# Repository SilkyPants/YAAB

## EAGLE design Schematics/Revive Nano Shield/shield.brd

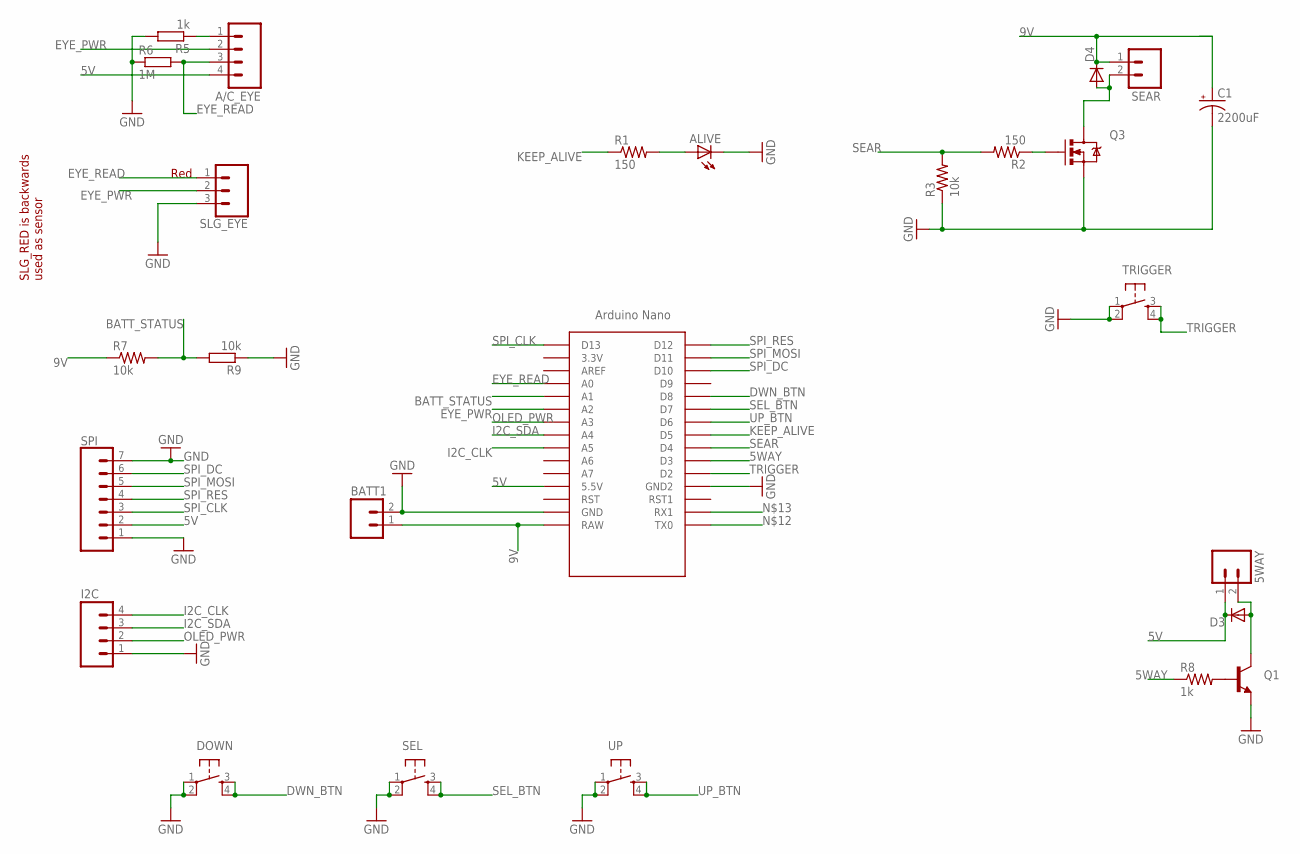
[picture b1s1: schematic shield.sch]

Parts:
5WAY: M02PTH; 1X02
A/C_EYE: M04PTH; 1X04
ALIVE: LED3MM
BATT1: M02PTH; 1X02
C1: 2200uF; CPOL-RADIAL-1000UF-25V
D3, D4: DIODEPTH; DIODE-1N4001
DOWN: TAC_SWITCHPTH; TACTILE-PTH
I2C: M04PTH; 1X04
Q1: TRANSISTOR_NPNTO-92-AMMO; TO-92-AMMO
Q3: MOSFET-NCHANNELPTH2; TO220V
R1, R2: 150; AXIAL-0.4
R3, R7: 10k; AXIAL-0.4
R5: 1k; 0309V
R6: 1M; 0309V
R8: 1k; AXIAL-0.4
R9: 10k; 0309V
SEAR: M02PTH; 1X02
SEL: TAC_SWITCHPTH; TACTILE-PTH
SLG_EYE: CONN_03; 1X03
SPI: CONN_07; 1X07
TRIGGER: TAC_SWITCHPTH; TACTILE-PTH
U$5: NANO
UP: TAC_SWITCHPTH; TACTILE-PTH

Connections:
5V: 5WAY.1, A/C_EYE.4, D3.C, SPI.2, U$5.5V (5.5V)
5WAY: R8.P$1 (1), U$5.D3
9V: BATT1.1, C1.1 (+), D4.C, R7.P$1 (1), SEAR.1, U$5.RAW
BATT_STATUS: R7.P$2 (2), R9.2, U$5.A1
DWN_BTN: DOWN.3, DOWN.4, U$5.D8
EYE_GND: A/C_EYE.1, R5.1
EYE_PWR: A/C_EYE.2, SLG_EYE.2, U$5.A2
EYE_READ: A/C_EYE.3, R6.2, SLG_EYE.1, U$5.A0
GND: ALIVE.K (C), BATT1.2, C1.2 (-), DOWN.1, DOWN.2, I2C.1, Q1.1 (E), Q3.3 (S), R3.P$1 (1), R5.2, R6.1, R9.1, SEL.1, SEL.2, SLG_EYE.3, SPI.1, SPI.7, TRIGGER.1, TRIGGER.2, U$5.GND, U$5.GND1 (GND2), UP.1, UP.2
I2C_CLK: I2C.4, U$5.A5
I2C_SDA: I2C.3, U$5.A4
KEEP_ALIVE: R1.P$1 (1), U$5.D5
unnamed: Q1.2 (B), R8.P$2 (2)
unnamed: ALIVE.A, R1.P$2 (2)
unnamed: Q3.1 (G), R2.P$1 (1)
unnamed: D4.A, Q3.2 (D), SEAR.2
unnamed: 5WAY.2, D3.A, Q1.3 (C)
OLED_PWR: I2C.2, U$5.A3
SEAR: R2.P$2 (2), R3.P$2 (2), U$5.D4
SEL_BTN: SEL.3, SEL.4, U$5.D7
SPI_CLK: SPI.3, U$5.D13
SPI_DC: SPI.6, U$5.D10
SPI_MOSI: SPI.5, U$5.D11
SPI_RES: SPI.4, U$5.D12
TRIGGER: TRIGGER.3, TRIGGER.4, U$5.D2
UP_BTN: U$5.D6, UP.3, UP.4

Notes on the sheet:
SLG_RED is backwards used as sensor
Red

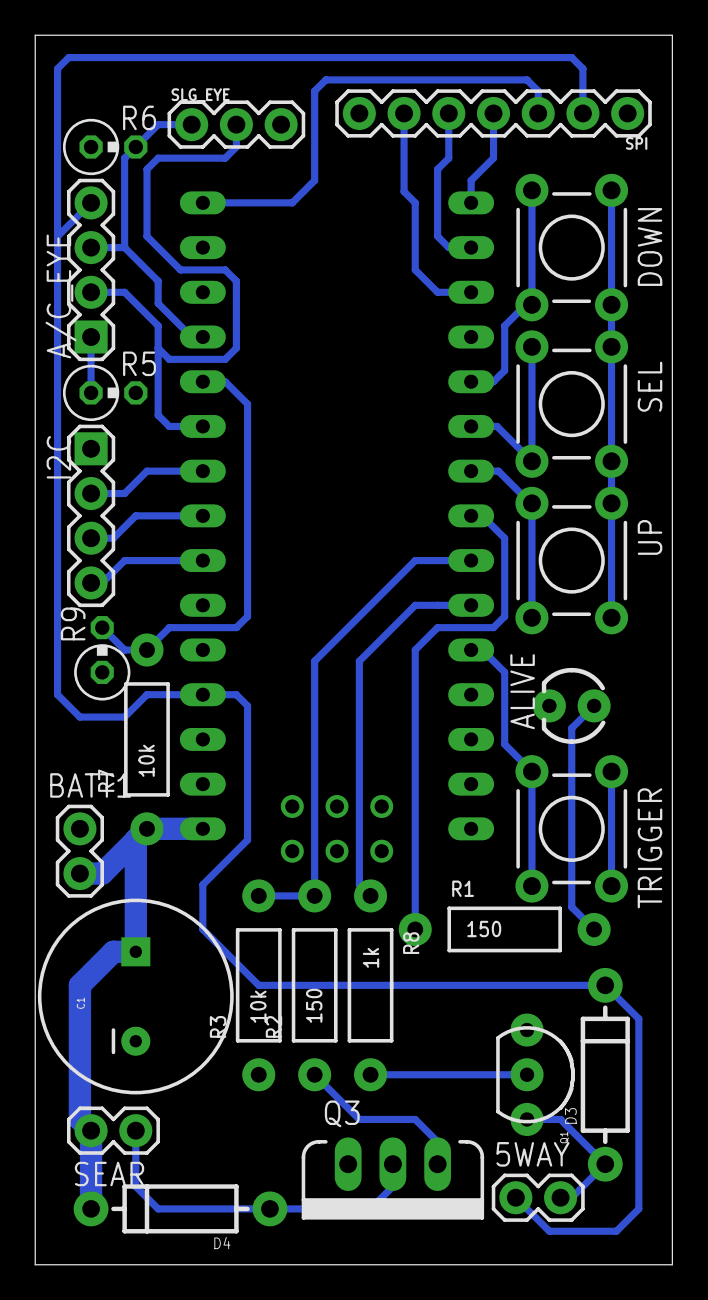
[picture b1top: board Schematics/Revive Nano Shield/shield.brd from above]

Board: 2 copper layers, 36.2 x 69.8 mm, 26 parts (0 on the bottom side), 26 nets.

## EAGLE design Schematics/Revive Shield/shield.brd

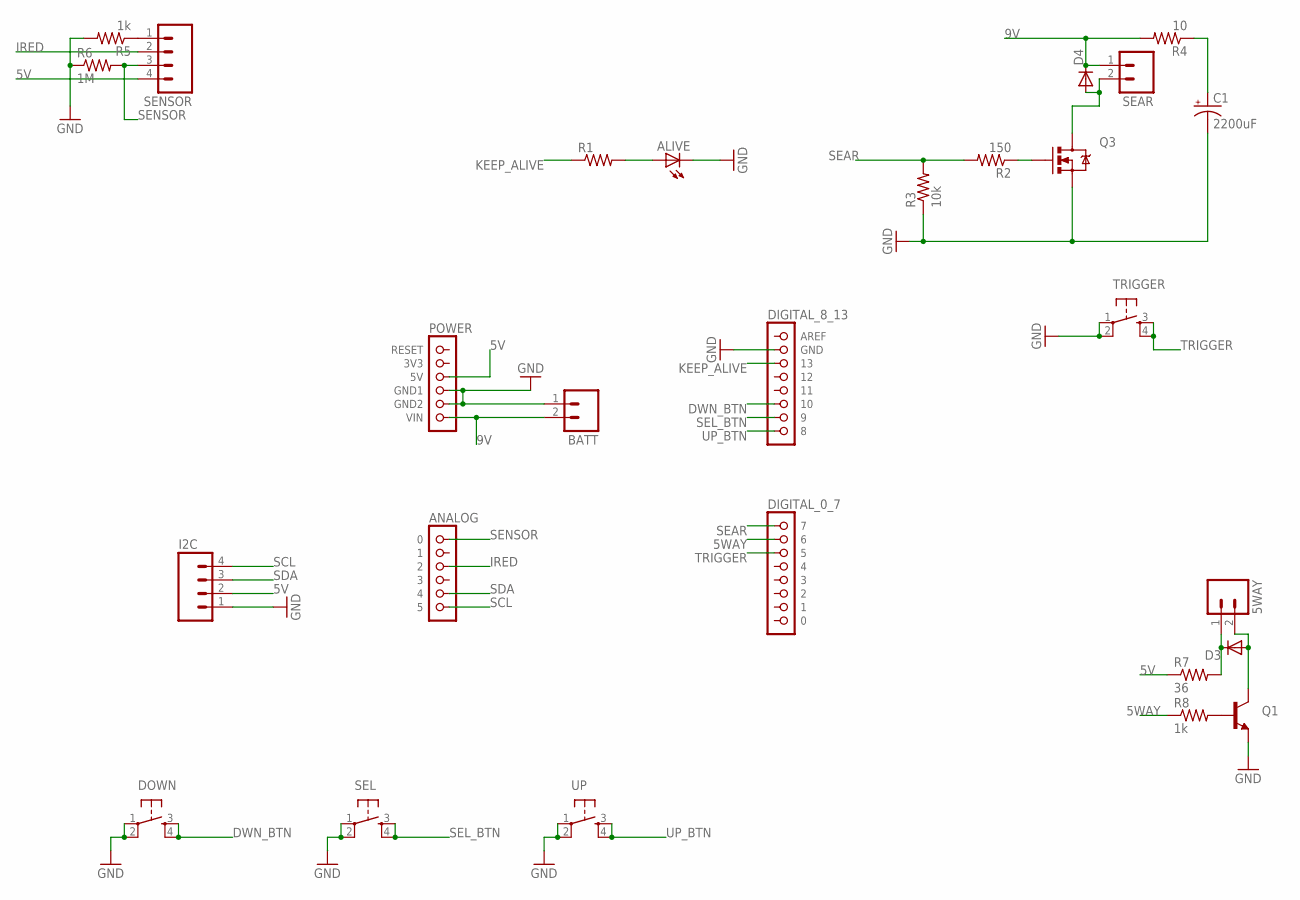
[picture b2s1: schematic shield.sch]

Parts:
5WAY: M02PTH; 1X02
ALIVE: LED3MM
BATT: M02PTH; 1X02
C1: 2200uF; CPOL-RADIAL-1000UF-25V
D3, D4: DIODEPTH; DIODE-1N4001
DOWN: TAC_SWITCHPTH; TACTILE-PTH
I2C: M04PTH; 1X04
Q1: TRANSISTOR_NPNTO-92-AMMO; TO-92-AMMO
Q3: MOSFET-NCHANNELPTH2; TO220V
R1: RESISTORPTH-1/4W; AXIAL-0.4
R2: 150; AXIAL-0.4
R3: 10k; AXIAL-0.4
R4: 10; AXIAL-0.4
R5, R8: 1k; AXIAL-0.4
R6: 1M; AXIAL-0.4
R7: 36; AXIAL-0.4
SEAR: M02PTH; 1X02
SEL: TAC_SWITCHPTH; TACTILE-PTH
SENSOR: M04PTH; 1X04
TRIGGER: TAC_SWITCHPTH; TACTILE-PTH
U$1: POWER; 1X06
U$2: ANALOG; 1X06
U$3: DIGITAL_0_7; 1X08
U$4: DIGITAL_8_13; 1X08
UP: TAC_SWITCHPTH; TACTILE-PTH

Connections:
5V: I2C.2, R7.P$1 (1), SENSOR.4, U$1.3 (5V)
5WAY: R8.P$1 (1), U$3.2 (6)
9V: BATT.2, D4.C, R4.P$2 (2), SEAR.1, U$1.6 (VIN)
DWN_BTN: DOWN.3, DOWN.4, U$4.6 (10)
GND: ALIVE.K (C), BATT.1, C1.2 (-), DOWN.1, DOWN.2, I2C.1, Q1.1 (E), Q3.3 (S), R3.P$1 (1), R5.P$2 (2), R6.P$1 (1), SEL.1, SEL.2, TRIGGER.1, TRIGGER.2, U$1.4 (GND1), U$1.5 (GND2), U$4.2 (GND), UP.1, UP.2
IRED: SENSOR.2, U$2.3 (2)
KEEP_ALIVE: R1.P$1 (1), U$4.3 (13)
unnamed: Q1.2 (B), R8.P$2 (2)
unnamed: ALIVE.A, R1.P$2 (2)
unnamed: Q3.1 (G), R2.P$1 (1)
unnamed: C1.1 (+), R4.P$1 (1)
unnamed: 5WAY.1, D3.C, R7.P$2 (2)
unnamed: R5.P$1 (1), SENSOR.1
unnamed: D4.A, Q3.2 (D), SEAR.2
unnamed: 5WAY.2, D3.A, Q1.3 (C)
SCL: I2C.4, U$2.6 (5)
SDA: I2C.3, U$2.5 (4)
SEAR: R2.P$2 (2), R3.P$2 (2), U$3.1 (7)
SEL_BTN: SEL.3, SEL.4, U$4.7 (9)
SENSOR: R6.P$2 (2), SENSOR.3, U$2.1 (0)
TRIGGER: TRIGGER.3, TRIGGER.4, U$3.3 (5)
UP_BTN: U$4.8, UP.3, UP.4

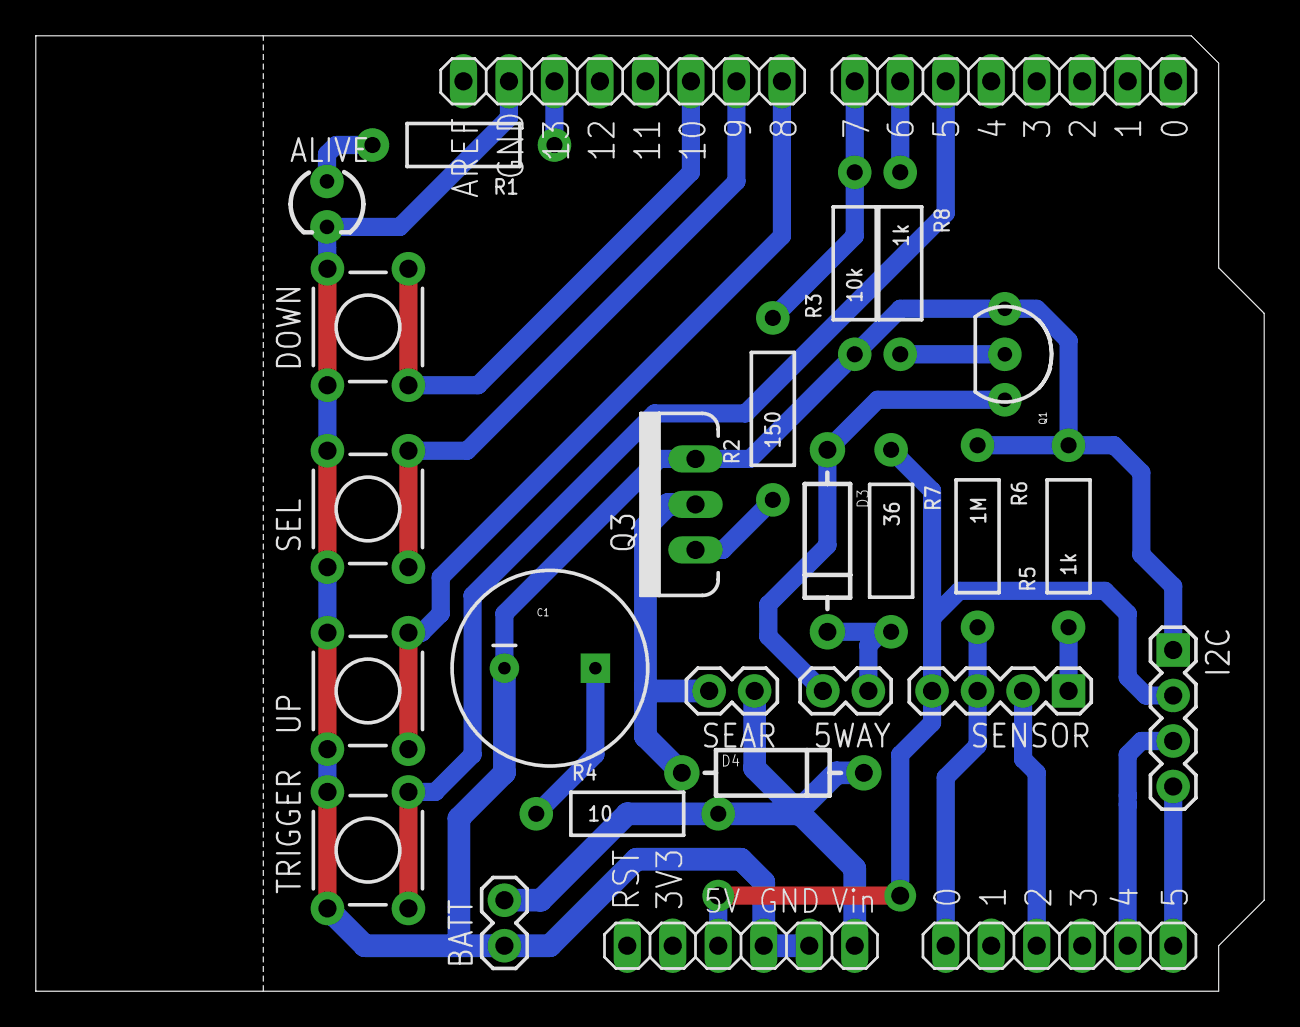
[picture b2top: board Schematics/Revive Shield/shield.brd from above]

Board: 2 copper layers, 68.6 x 53.3 mm, 27 parts (0 on the bottom side), 22 nets.

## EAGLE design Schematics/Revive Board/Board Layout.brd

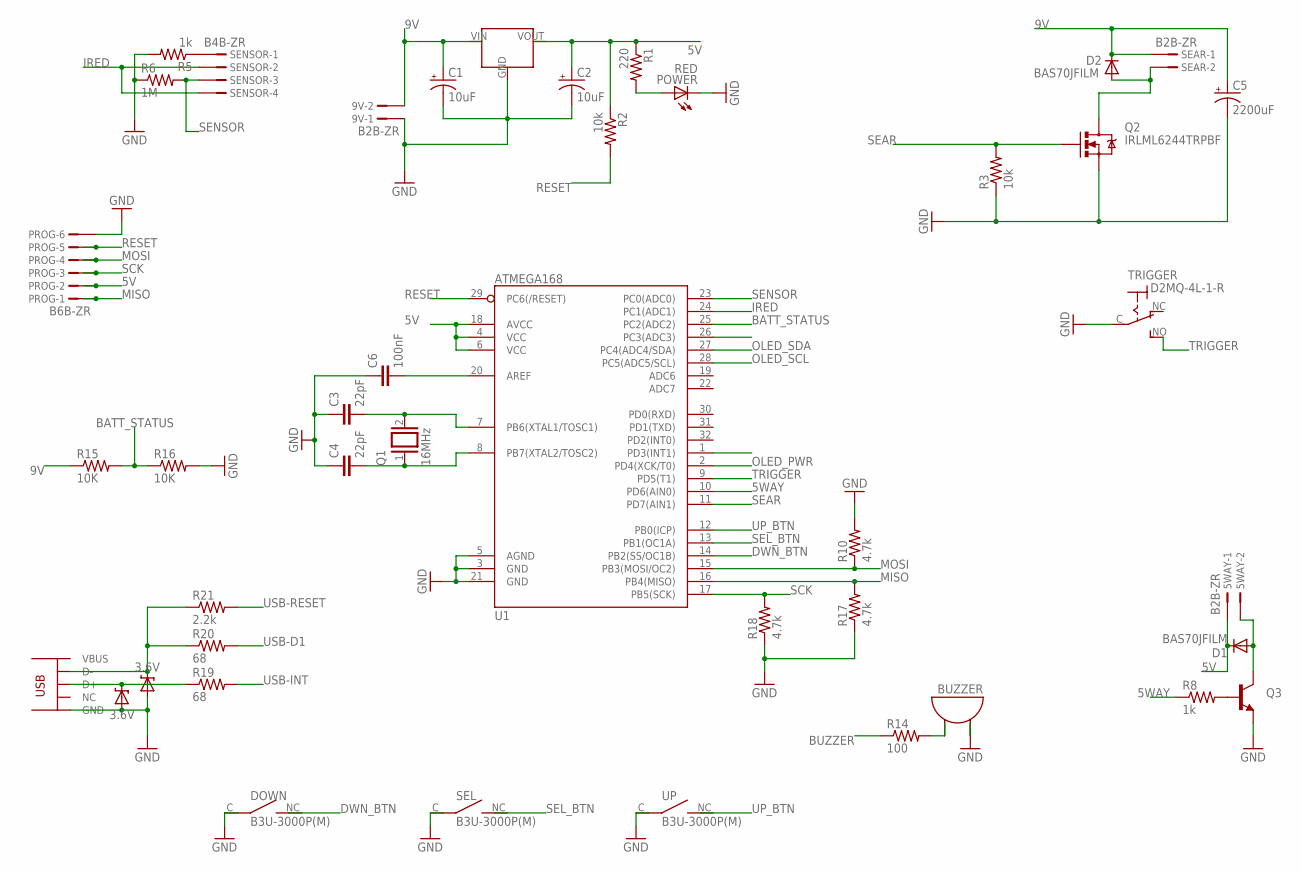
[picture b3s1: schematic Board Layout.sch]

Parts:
3.6V: 3.6V; SOD-323
5WAY, 9V: B2B-ZR
BUZZER: KPEG171
C1, C2: 10uF; AVES***M**B
C3, C4: 22pF; 0402-CAP
C5: 2200uF; AVES***M**B
C6: 100nF; 0402-CAP
D1, D2: BAS70JFILM; SOD-323
DOWN: B3U-3000P(M)
MAX603: 7805; SOT-89
POWER: RED; CHIP-LED0603
PROG: B6B-ZR
Q1: 16MHz; QS
Q2: IRLML6244TRPBF; SOT23-3
Q3: TRANSISTOR_NPNSOT89; SOT89
R1: 220; R0603
R2, R3: 10k; R0603
R5, R8: 1k; R0603
R6: 1M; R0603
R10, R17, R18: 4.7k; R0603
R14: 100; R0603
R15, R16: 10K; R0603
R19, R20: 68; R0603
R21: 2.2k; R0603
SEAR: B2B-ZR
SEL: B3U-3000P(M)
SENSOR: B4B-ZR
TRIGGER: D2MQ-4L-1-R
U1: ATMEGA168; TQFP32-08
U$2: 3.6V; SOD-323
U$3: USB-MINI-B-VERT
UP: B3U-3000P(M)

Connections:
5V: 5WAY.1, C2.P$1+ (+), D1.1 (C), MAX603.VOUT (OUT), PROG.2, R1.1, R2.1, U1.4 (VCC), U1.6 (VCC), U1.18 (AVCC)
5WAY: R8.1, U1.10 (PD6(AIN0))
9V: 9V.2, C1.P$1+ (+), C5.P$1+ (+), D2.1 (C), MAX603.VIN (IN), R15.1, SEAR.1
BATT_STATUS: R15.2, R16.1, U1.25 (PC2(ADC2))
BUZZER: R14.1
DWN_BTN: DOWN.NC (NO), U1.14 (PB2(SS/OC1B))
GND: 3.6V.2 (A), 9V.1, BUZZER.2 (PB2), C1.P$2- (-), C2.P$2- (-), C3.1, C4.1, C5.P$2- (-), C6.1, DOWN.C, POWER.C, PROG.6, Q2.2 (S), Q3.3 (E), R3.1, R5.2, R6.1, R10.2, R16.2, R17.1, R18.1, SEL.C, TRIGGER.C, U1.3 (GND), U1.5 (AGND), U1.21 (GND), U$2.2 (A), UP.C
IRED: SENSOR.2, SENSOR.4, U1.24 (PC1(ADC1))
MISO: PROG.1, R17.2, U1.16 (PB4(MISO))
MOSI: PROG.4, R10.1, U1.15 (PB3(MOSI/OC2))
unnamed: C3.2, Q1.2, U1.7 (PB6(XTAL1/TOSC1))
unnamed: C4.2, Q1.1, U1.8 (PB7(XTAL2/TOSC2))
unnamed: C6.2, U1.20 (AREF)
unnamed: POWER.A, R1.2
unnamed: D2.2 (A), Q2.3 (D), SEAR.2
unnamed: R5.1, SENSOR.1
unnamed: R20.1, R21.1, U$2.1 (C)
unnamed: 3.6V.1 (C), R19.1
unnamed: 5WAY.2, D1.2 (A), Q3.2 (C)
unnamed: Q3.1 (B), R8.2
unnamed: BUZZER.1 (PB1), R14.2
OLED_PWR: U1.2 (PD4(XCK/T0))
OLED_SCL: U1.28 (PC5(ADC5/SCL))
OLED_SDA: U1.27 (PC4(ADC4/SDA))
RESET: PROG.5, R2.2, U1.29 (PC6(/RESET))
SCK: PROG.3, R18.2, U1.17 (PB5(SCK))
SEAR: R3.2, U1.11 (PD7(AIN1))
SEL_BTN: SEL.NC (NO), U1.13 (PB1(OC1A))
SENSOR: R6.2, SENSOR.3, U1.23 (PC0(ADC0))
TRIGGER: TRIGGER.NO (S), U1.9 (PD5(T1))
UP_BTN: U1.12 (PB0(ICP)), UP.NC (NO)
USB-D1: R20.2
USB-INT: R19.2
USB-RESET: R21.2

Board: 2 copper layers, 42 parts (0 on the bottom side), 27 nets, no tracks yet.

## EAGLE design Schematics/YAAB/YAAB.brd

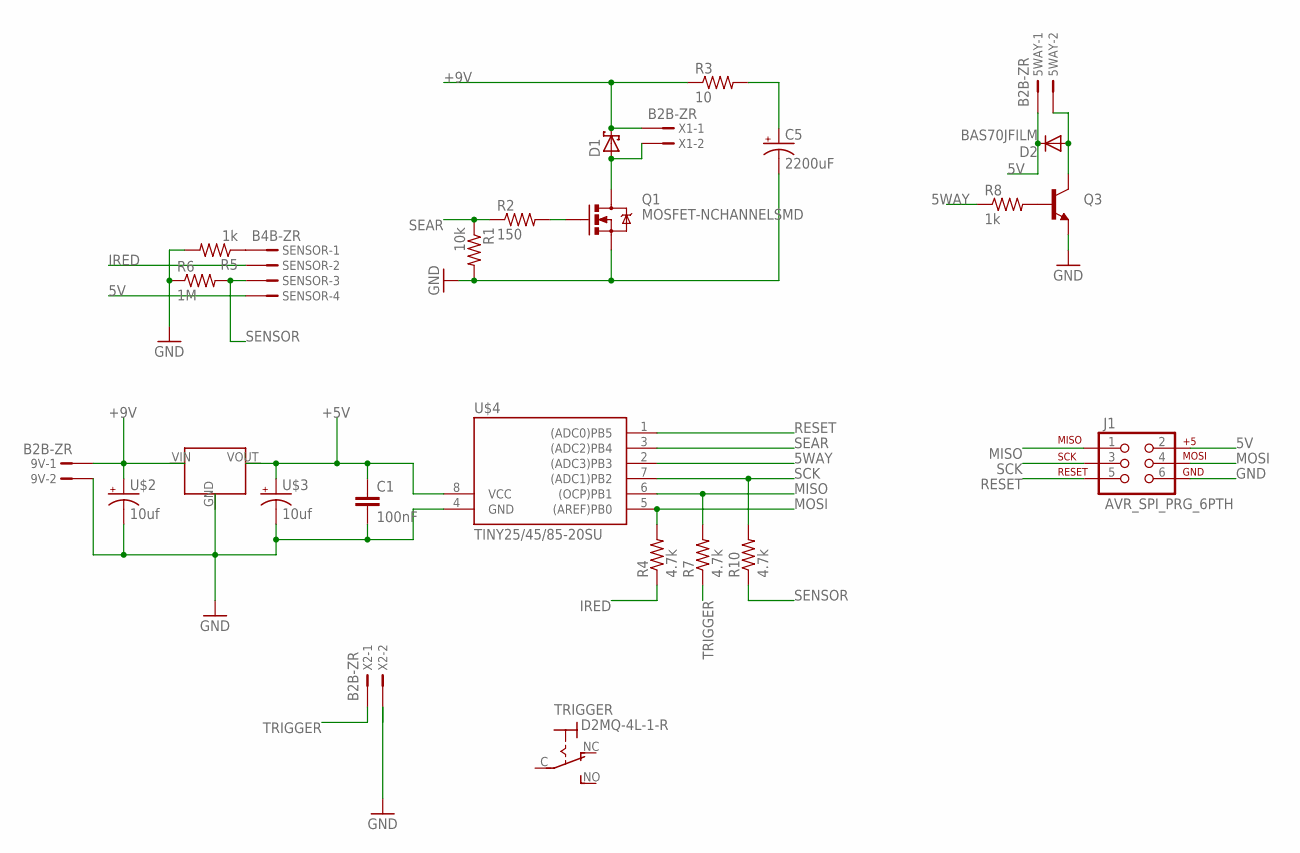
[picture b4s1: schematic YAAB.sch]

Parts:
5WAY, 9V: B2B-ZR; B2B-ZR@1
C1: 100nF; CAP-PTH-SMALL-KIT
C5: 2200uF; AVES***M**B
D1: SCHOTTKY-DIODESMC; SMC
D2: BAS70JFILM; SOD-323
J1: AVR_SPI_PRG_6PTH; 2X3
Q1: MOSFET-NCHANNELSMD; SOT23-3
Q3: TRANSISTOR_NPNSOT89; SOT89
R1: 10k; 0603-RES
R2: 150; 0603-RES
R3: 10; 0603-RES
R4, R7, R10: 4.7k; 1206
R5, R8: 1k; R0603
R6: 1M; R0603
SENSOR: B4B-ZR
TRIGGER: D2MQ-4L-1-R
U$1: L78M05C; SOT-89
U$2, U$3: 10uf; AVES***M**B
U$4: TINY25/45/85-20SU; SOIC8
X1: B2B-ZR; B2B-ZR@1
X2: B2B-ZR

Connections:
5V: 5WAY.1, D2.1 (C), J1.2, SENSOR.4
5WAY: R8.1, U$4.2 ((ADC3)PB3)
+5V: C1.1, U$1.VOUT (OUT), U$3.P$1+ (+), U$4.8 (VCC)
+9V: 9V.1, D1.C, R3.1, U$1.VIN (IN), U$2.P$1+ (+), X1.1
GND: 9V.2, C1.2, C5.P$2- (-), J1.6, Q1.2 (S), Q3.3 (E), R1.2, R5.2, R6.1, U$1.GND, U$2.P$2- (-), U$3.P$2- (-), U$4.4 (GND)
IRED: R4.1, SENSOR.2
MISO: J1.1, R7.2, U$4.6 ((OCP)PB1)
MOSI: J1.4, R4.2, U$4.5 ((AREF)PB0)
unnamed: Q1.1 (G), R2.2
unnamed: D1.A, Q1.3 (D), X1.2
unnamed: C5.P$1+ (+), R3.2
unnamed: R5.1, SENSOR.1
unnamed: 5WAY.2, D2.2 (A), Q3.2 (C)
unnamed: Q3.1 (B), R8.2
RESET: J1.5, U$4.1 ((ADC0)PB5)
SCK: J1.3, R10.2, U$4.7 ((ADC1)PB2)
SEAR: R1.1, R2.1, U$4.3 ((ADC2)PB4)
SENSOR: R6.2, R10.1, SENSOR.3
TRIGGER: R7.1, X2.1, X2.2

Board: 2 copper layers, 26 parts (0 on the bottom side), 19 nets, no tracks yet.

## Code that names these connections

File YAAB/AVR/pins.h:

/*
YAAB - Yet Another Autococker Board
Arduino based autococker board developed around the platform and ATMEL AVR
chips

Copyright (C) 2015  Dan Silk

This program is free software: you can redistribute it and/or modify
it under the terms of the GNU General Public License as published by
the Free Software Foundation, either version 3 of the License, or
(at your option) any later version.

This program is distributed in the hope that it will be useful,
but WITHOUT ANY WARRANTY; without even the implied warranty of
MERCHANTABILITY or FITNESS FOR A PARTICULAR PURPOSE.  See the
GNU General Public License for more details.

You should have received a copy of the GNU General Public License
along with this program.  If not, see <http://www.gnu.org/licenses/>.
*/

#pragma once

#include "../common.h"

#if defined(__AVR_ATtiny84__)

#define CYCLE_PORT PORTA
#define CYCLE_PORT_REG DDRA
#define CYCLE_PIN_REG PINA

#define EYE_PORT PORTA
#define EYE_PORT_REG DDRA

#elif defined(__AVR_ATtiny85__)

#if F_CPU > 8000000UL
    #error Cannot use an ATTiny*5 chip with a clock speed greater than 8Mhz. Not enough pins!
#endif

#define CYCLE_PORT PORTB
#define CYCLE_PORT_REG DDRB
#define CYCLE_PIN_REG PINB

#define EYE_PORT PORTB
#define EYE_PORT_REG DDRB

#define TIMSK0 TIMSK // As the ATTiny*5 does not refer to timer 0 as such

#elif defined( __AVR_ATmega328__ ) || defined( __AVR_ATmega328P__ )

#define CYCLE_PORT PORTD
#define CYCLE_PORT_REG DDRD
#define CYCLE_PIN_REG PIND

#define EYE_PORT PORTC
#define EYE_PORT_REG DDRC

#define INPUT_PORT PORTD
#define INPUT_PORT_REG DDRD
#define INPUT_PIN_REG PIND

#define OLED_PORT PORTB
#define OLED_PORT_REG DDRB

#else

#error Unsupported chip! Please edit pins.h to support your chosen AVR chip.

#endif

#if defined(__AVR_ATtiny25__) || defined(__AVR_ATtiny45__) || defined(__AVR_ATtiny85__)

// On Port B (0, 1, 2)
#define TRIGGER_PIN 0
#define PNEU_PIN 1
#define SEAR_PIN 2

// On Port B (3, 4)
#define EYE_PIN 3
#define IRED_PIN 4

#define OLED_PWR_PIN 5 // I2C

#define OLED_DC_PIN 2
#define OLED_RST_PIN 4

#elif defined( __AVR_ATmega328__ ) || defined( __AVR_ATmega328P__ )

// On Port D (5, 6, 7)
#define TRIGGER_PIN 2	// Arduino Pin 2
#define PNEU_PIN 3		// Arduino Pin 3
#define SEAR_PIN 4		// Arduino Pin 4

// On Port C (0, 2)
#define EYE_PIN 0		// Arduino Pin A0
#define IRED_PIN 1		// Arduino Pin A1

// On Port D (5-7)
#define UP_BUTTON_PIN 5	// Arduino Pin 5
#define OK_BUTTON_PIN 6	// Arduino Pin 6
#define DN_BUTTON_PIN 7	// Arduino Pin 7

#define OLED_PWR_PIN  5 // Arduino Pin 13 - I2C

#define OLED_DC_PIN 2   // Arduino Pin 10
#define OLED_RST_PIN 4  // Arduino Pin 12

#endif

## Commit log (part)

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2012-02-08 Initial Commit
    Currently sits in full auto mode - still researching best way to handle
    trigger bounce.
    Hard coded E-Blade Fast settings for testing purposes.
2012-02-08 First Pass Basics
    Moved trigger scanning into timer interrupt
    Added debounce to trigger
    Added a few more macros to aid programming
2012-02-09 Extended Fire Modes
    Added ability for firing on release and bursts
    Increased slow down timer
2012-02-09 Merging from work PC
    *Should* be able to run on ATTINY *4 and *5 chips - untested of course
    Added Visual Micro files to repository
2012-02-09 Missed the stage
2012-02-20 Split Cycle Values into two structures - one for timing and one for firing profiles (as the profiles will change but the timing should stay constant) Moved eyes out to global - might not be useful fo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
2012-02-20 removing redundant directory
2012-02-20 Added ipch and debug directory to ignore list
2012-02-20 Created readme so that the page looks pretty :D
2012-02-25 Memory Shuffling
    Moved booleans into byte with flags
    Timing code now has reset for factory settings
2012-02-26 Cycle now using states
    Simple state machine setup for marker cycling, also using unused bits
    for more options
2012-02-27 Started work on profiles - still stored in flash
2012-02-27 Broken down settings into more usable structs with bitfields
2012-02-27 Start on Eye logic and fixed bug with setting shots to fire
2012-04-17 Bit of tidy work - trying to fix broken-ness Hope to get it running again
2012-04-18 using setting
2012-04-19 More rework Mostly fat trimming and restructure
2012-04-20 Moved code into seperate files for easier management
2012-04-20 Created gh-pages branch via GitHub
2012-04-20 Commiting another page
2012-04-20 More code tidy
2012-04-20 More code tidying
2012-04-20 Now building in Arduino
2012-04-23 Bit Alignment New Marcos Code Compression Actually using flags
2012-04-23 Last minute changes
2012-04-24 Kinda working - baby steps
2012-04-25 Enabled Serial for debugging
2012-04-26 More shuffling of settings Added ability to start/stop timer
2012-04-26 Removed bolt seen for now
2012-04-27 Start of new Task based system Idea is to have a list of tasks the cycle needs to do to complete, then only call the current task in the ISR
2012-04-27 Actually using an IntervalLapse Task and fixed a typo
2012-04-27 Fixed up a few things Added Auto Reset to Interval Task
2012-04-27 Missed the bus
2012-04-27 Pin Change Task now working properly with debounce
2012-04-27 Trying to reintergrate old stuff
    Looks like a bit of a rewrite is in order :S
2012-04-27 Now Cycling
    No Release firing on Reactive :S
2012-04-28 Reactive Fire Modes/ Fire on trigger release now working
    Also realised that all my flags are wasting a bit :S
2012-04-28 All firing modes working again
    Needed to set fire mode flags
2012-04-30 Created start of Game Timer class More work with Tasks, created another class for Time Critical Tasks Added Comment to show values and their ranges in settings Removed old interrupt code as it's no l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
2012-04-30 Removed useless inlines
2012-05-01 Added Eye Task Moved everything to task system
2012-05-03 Added Training Mode
2012-05-05 All working again
    Few silly mistakes - need to stop working without the board
2012-09-21 Reshuffle of code
    Moved feature defines into common for easier changing
    Added ability to build without Arduino libraries - saves ~300 bytes
2012-09-21 Refactored to make it more C++ friendly
    Headers declare, Cpp Defines
2012-09-21 More refactoring
    ADC and Timer functions now moved to cpp files - code as bloated a
    little
2012-09-21 Junk files
2012-09-28 Testing Arduino mode
    Also changed for loop in main to while - reads better
2012-11-06 Few small changes
    Upped the max ROF - not sure if I need the space
    Removed hard coded port
2012-11-15 Few little things
    Added Get for current eye value
    Fixed up serial code for eye
    Added null to time string
2012-11-20 Simplified the game timer
    Split the timers into a single class, and added reset functionality
    Renamed files to reflect what is inside
2012-11-20 Bit of commenting
2012-12-13 Added processor define and tidy
2012-12-18 Tidied up timer code, and some error reporting
    Added catch if trying to compile for an ATTiny*5 with a clock speed
    greater than 8MHz
    Timer code now cleaner in actual definition
    Added #defines for supported chips, this should be removed later
2013-12-05 Updated to build on latest version of Arduino IDE
    Had to rename main.h/.cpp as it seems that the naming causes the Arduino IDE to not compile a main function.
2013-12-06 Cleaned up warnings
2013-12-06 Renamed mainx to marker to make intentions clearer Fixed spelling mistake
2013-12-06 Removed virtual destructor on Task class - saves a fair bit of program size! Added solution files for Atmel Studio 6.1 to build both Arduino and AVR (no Arduino libs) versions
2013-12-08 Removed unsupported chips (due to insufficient RAM) Seems Windows has added new lines to the end of files
2013-12-09 Getting OLED to operate in system
2013-12-09 Rendering nicely with CRIUS OLED
2013-12-09 Moved font and Borders to program space to save memory Initialised buffer to borders for now - do we really need it? Fixed drawString/drawChar to access program space for characters Put test menu in 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
2013-12-09 Swapped to normal display Moved render into loop to update display ASAP
2013-12-10 Added support for larger fonts Added readable defines for OLED commands
2013-12-10 Added ability to draw strings in a given font from programming space Added function to fill/clear an area of the buffer Added simple demo for battery level and drain
2013-12-15 Updated copyright Updated settings to use uint_ types for easier size recognition
2013-12-23 ADC now working for eye - need to rethink free running if we want to use battery monitor in future.
2013-12-24 Moved trigger pin to pin 5, as it’s not running on an interrupt anymore.
2013-12-30 Created Arduino solution for AVR Studio, compatible with Arduino build chain.
2013-12-30 Missed files
2014-01-04 Renamed projects so the Arduino build can work with the Arduino IDE Arduino Atmel Studio build adds the USE_ARDUINO flag in the project
2015-05-04 Created Xcode project for use with x-avr/AVR Crosspack (https://github.com/jawher/xavr) Moved source to separate folder - Arduino .ino file must live there to keep it building. Moved AVR main functio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
2015-05-04 Added EagleCAD schematics and board designs Added OLED design and font files Fixed warning in crius_oled drawString function
2015-05-04 Fixed Full Auto flag issue Code tidy
2015-05-04 Moved display code into new UI files Fixed issue where AUTO_ALLOWED was false causing broken builds Fixed PinState task to reference the correct port registry/pins
2015-05-05 Updated Visual Studio project files to work with the latest SDKs and plugins
    Arduino 1.6.3
    Visual Micro (pre release)
    Visual Studio Community 2013
2015-05-05 Strings belong with the UI
2015-05-05 Moved eye reading to eye task Attempting to read in the UI now Added function to draw character at a given location Moved battery draw function to UI Code and Comment Tidy
2015-05-05 No longer committing Visual Micro files Update project file
2015-05-05 Started working towards menu screens
2015-05-06 Moved marker code into separate class
2015-05-06 Removed Visual Micro generated files Updated project
2015-05-07 Regenerated font file and added export file to repository
2015-05-07 Reordered strings and created string table
2015-05-07 Moved OLED functions into own class, more RAM savings Created string tables for strings
2015-05-07 removing old comments
2015-05-07 REnamed profiles to modes, to better reflect their use Moved modes to program space Simple attempt to load profile from program space
2015-05-07 Updated xsl to output correct data type
2015-05-07 Added BPS character (/) to BPS Font
2015-05-07 Fixed build issues Fixed display not rendering in the correct locations
2015-05-07 Marker modes loading correctly out of program space
2015-05-07 Updated AVR Studio project Moved timer string to get passed in as required
2015-05-07 Updated font so ball animation could play more efficiently Renamed AVR Studio project
2015-05-07 Code tidy
2015-05-07 Added C++ helper for abstract classes
2015-05-08 Added initial UI design strings to string table Created simple Menu Screen base class Moved virtual C++ helper to common.cpp, as main.cpp is not build in Arduino IDE
2015-05-08 Missed last commit
2015-05-08 Fixed Xcode build
2015-05-10 Moved UI functions into class Set up simple state machine stubs
2015-05-11 Updated copyright messages Added UI state files Spaces now render to clear space
2015-05-11 Added state machine Created button class to encapsulate button states Added buttons to UI class
2015-05-11 Fixed issues with button logic Increased held button time Made simple menu loop
2015-05-12 Updated font Added blank UI states Added cursor functionality to the UI instead of the states
2015-05-12 Added colon (:) to BPS Font
2015-05-12 Updated Atmel studio project Fixed warnings and cursor limits
2015-05-13 Moved Timer variables into packed struct, and saved 3 bytes
2015-05-13 Implemented simple performance check to only upload new buffer when it was dirty
2015-05-13 Added cursor reset function to help with option selection between screen Added Setup menu
2015-07-26 Fixed issue where menu option scrolling would stop when button enters HELD state Created simple state stack to allow common back button across states. Added missing UI state files to Xcode project Fi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
2015-12-15 Fixed case typo in BreechEyesTask header and changed Make file to search for avr dev tools, instead of hard coded paths
2016-01-29 Updated OLED design
2016-01-29 Moving files around into a more descriptive folder structure
    This will break the XCode and Visual/Atmel studio files for now
2016-01-29 Added source files as folder references - still issues with makefile
2016-01-29 Removed Build directory removal, and changed foreach to for loop
    OSX does not have foreach unfortunately
2016-02-01 Makefile compiles on OSX command line again
2016-02-01 Fixed make file for compilation on Arch
    Needed to add -fno-use-cxa-atexit to stop build complaints, as it seems the newer versions of gcc have swapped the default behavior
    Removed strict prototypes, as it is not required for C++ projects
2016-02-03 Compiling in Xcode again Added user data folder to ignore file Added CrossPack to Xcode project PATH variable Added Logging to check which binaries are loaded for utilities
2016-02-03 Changed Xcode project to reference the source folder, to ensure all code files are included
2016-05-26 Fixes compile errors after moving files around
2016-05-26 Adds Arduino component library, and Nano board schematic
2016-05-26 Adds prompt in makefile to get user to enter programmer device. Untested in Xcode
2016-05-26 Adds ability for Xcode to set AVRDUDE_PORT from build settings
2016-05-26 Updates nano design to be more compact
2016-05-26 Updates nano design so USB port is accessible while connected
2016-05-26 Fixes build issues on Linux
2016-05-27 Changes makefile to be more verbose with avrdude output, and forces baudrate for upload
2016-05-27 Reworks pins to match with new Nano board design
2016-09-16 Moved around connectors to make them more accessible
2017-10-15 Removed unnecessary files
2017-10-15 Fixed issue where screen would not get marked as Not Dirty after write
2017-10-25 Added break beam test sketch
2017-10-26 Added VSCode settings for C++ files
2017-10-28 Moved Break Beam test into Test folder outside of main project
2017-10-28 Added self contained test for SPI OLED communication.
2017-10-28 Fixed up warning and problems with VSCode on OSX
2017-10-28 Ported SPI OLED test back into program, and renamed OLED class and files to match the processor. Still needs a little work to be back 100%
2017-10-28 Tweaked board layout to fit everything nicer
2017-10-28 Project now uses SPI for OLED, and added required transfer calls to send commands/data
2017-10-28 Changed input pins as not to conflict with SPI

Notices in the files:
parts and their libraries:
SparkFun-Connectors: Licensing: Creative Commons ShareAlike 4.0 International - https://creativecommons.org/licenses/by-sa/4.0
SparkFun: Licensing: CC v3.0 Share-Alike You are welcome to use this library for commercial purposes.
